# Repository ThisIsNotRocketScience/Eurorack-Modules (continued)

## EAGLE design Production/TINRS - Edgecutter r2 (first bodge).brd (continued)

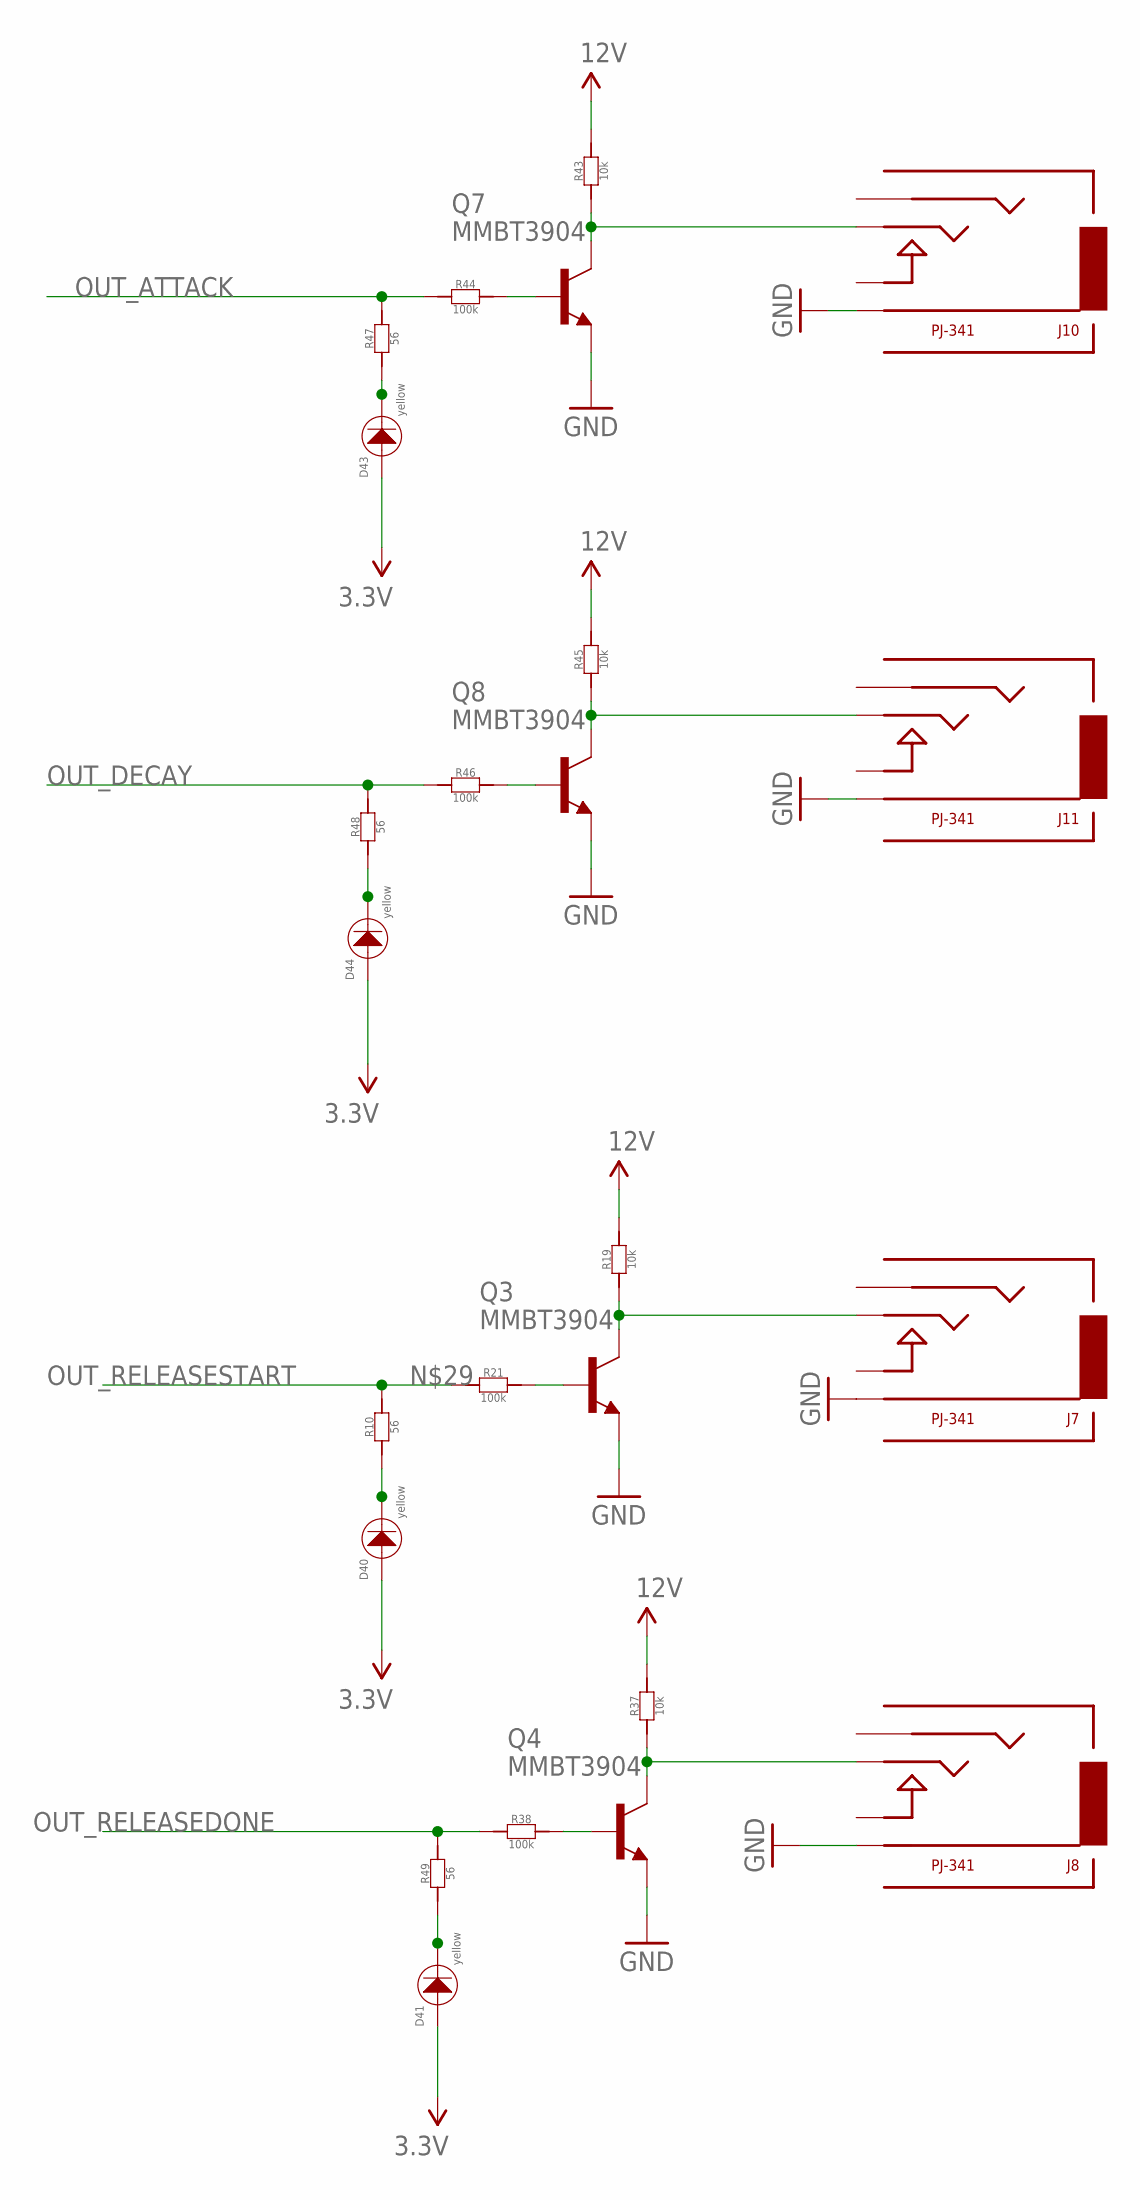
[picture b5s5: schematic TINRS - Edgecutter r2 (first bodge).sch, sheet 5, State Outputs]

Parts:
D40, D41, D43, D44: yellow; 3MMLED
J7, J8, J10, J11: PJ-341; 3.5MM-JACK-SWITCH-13MM-OUTPUT
Q3, Q4, Q7, Q8: MMBT3904; SOT23-BEC; MPN PMBT3904,215
R10, R47, R48, R49: 56; R0603
R19, R37, R43, R45: 10k; R0603
R21, R38, R44, R46: 100k; R0603

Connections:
3.3V: D40.+, D41.+, D43.+, D44.+; also elsewhere on the board
12V: R19.2, R37.2, R43.2, R45.2; also elsewhere on the board
D21: D43.-, R47.1
GND: J7.RING@3 (RING), J8.RING@3 (RING), J10.RING@3 (RING), J11.RING@3 (RING), Q3.E, Q4.E, Q7.E, Q8.E; also elsewhere on the board
unnamed: D40.-, R10.1
unnamed: Q3.B, R21.2
unnamed: J7.TIP@3 (TIP), Q3.C, R19.1
unnamed: D41.-, R49.1
unnamed: D44.-, R48.1
unnamed: Q4.B, R38.2
unnamed: J8.TIP@3 (TIP), Q4.C, R37.1
unnamed: Q7.B, R44.2
unnamed: J10.TIP@3 (TIP), Q7.C, R43.1
unnamed: Q8.B, R46.2
unnamed: J11.TIP@3 (TIP), Q8.C, R45.1
OUT_ATTACK: R44.1, R47.2; also elsewhere on the board
OUT_DECAY: R46.1, R48.2; also elsewhere on the board
OUT_RELEASEDONE: R38.1, R49.2; also elsewhere on the board
OUT_RELEASESTART: R10.2, R21.1; also elsewhere on the board

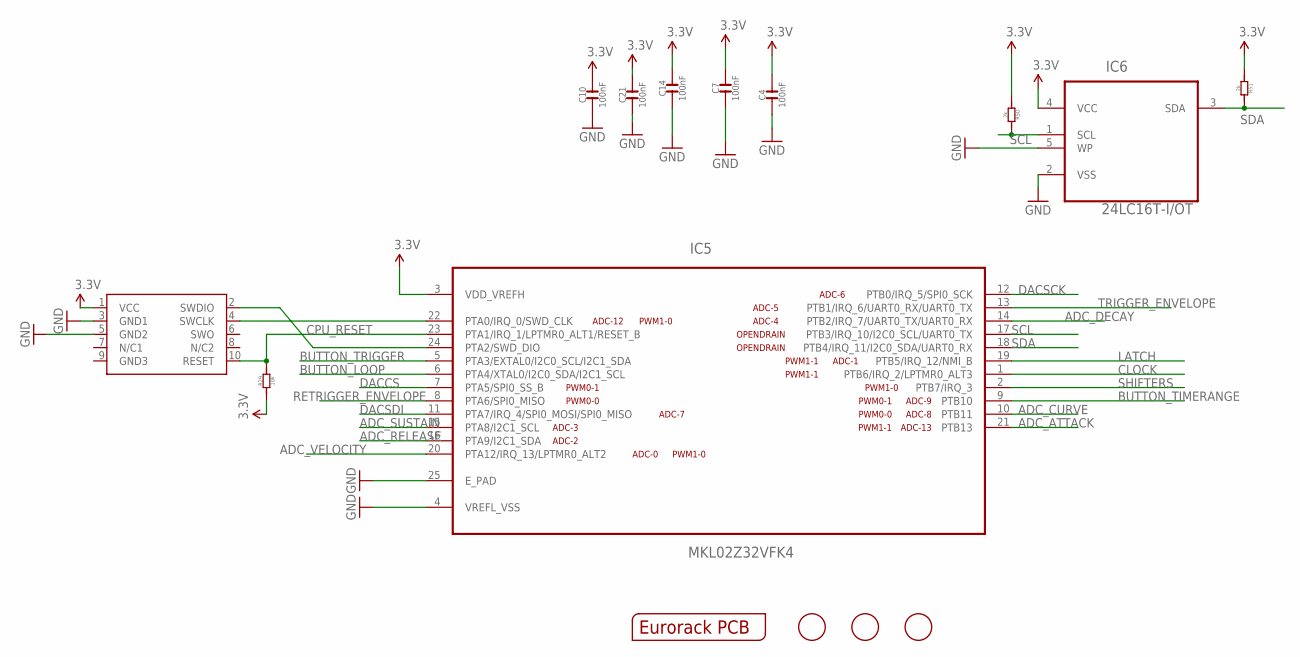
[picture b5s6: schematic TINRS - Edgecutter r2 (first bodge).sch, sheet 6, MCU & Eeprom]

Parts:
C4, C7, C10, C14, C21: 100nF; C0603; MPN MC0603F104Z160CT
FID1, FID2, FID3: FIDUCIAL; FIDUCIAL_1MM
IC5: MKL02Z32VFK4; QFN50P400X400X100-25N
IC6: 24LC16T-I/OT; SOT95P290X145-5N; MPN 24LC16T-I/OT
OUTLINE: EURORACK_PCB12HP; EURORACK12HPPCB
R29: 10k; R0603
R50, R51: 2k; R0603
SWD1: CORTEX_SWD; M50-3600542

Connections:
3.3V: C4.2, C7.2, C10.2, C14.2, C21.2, IC5.3 (VDD_VREFH), IC6.4 (VCC), R29.1, R50.1, R51.1, SWD1.1 (VCC); also elsewhere on the board
ADC_ATTACK: IC5.21 (PTB13); also elsewhere on the board
ADC_CURVE: IC5.10 (PTB11); also elsewhere on the board
ADC_DECAY: IC5.14 (PTB2/IRQ_7/UART0_TX/UART0_RX); also elsewhere on the board
ADC_RELEASE: IC5.16 (PTA9/I2C1_SDA); also elsewhere on the board
ADC_SUSTAIN: IC5.15 (PTA8/I2C1_SCL); also elsewhere on the board
ADC_VELOCITY: IC5.20 (PTA12/IRQ_13/LPTMR0_ALT2); also elsewhere on the board
BUTTON_LOOP: IC5.6 (PTA4/XTAL0/I2C0_SDA/I2C1_SCL); also elsewhere on the board
BUTTON_TIMERANGE: IC5.9 (PTB10); also elsewhere on the board
BUTTON_TRIGGER: IC5.5 (PTA3/EXTAL0/I2C0_SCL/I2C1_SDA); also elsewhere on the board
CLOCK: IC5.1 (PTB6/IRQ_2/LPTMR0_ALT3); also elsewhere on the board
CPU_RESET: IC5.23 (PTA1/IRQ_1/LPTMR0_ALT1/RESET_B), R29.2, SWD1.10 (RESET)
DACCS: IC5.7 (PTA5/SPI0_SS_B); also elsewhere on the board
DACSCK: IC5.12 (PTB0/IRQ_5/SPI0_SCK); also elsewhere on the board
DACSDI: IC5.11 (PTA7/IRQ_4/SPI0_MOSI/SPI0_MISO); also elsewhere on the board
GND: C4.1, C7.1, C10.1, C14.1, C21.1, IC5.4 (VREFL_VSS), IC5.25 (E_PAD), IC6.2 (VSS), IC6.5 (WP), SWD1.3 (GND1), SWD1.5 (GND2); also elsewhere on the board
LATCH: IC5.19 (PTB5/IRQ_12/NMI_B); also elsewhere on the board
RETRIGGER_ENVELOPE: IC5.8 (PTA6/SPI0_MISO); also elsewhere on the board
SCL: IC5.17 (PTB3/IRQ_10/I2C0_SCL/UART0_TX), IC6.1 (SCL), R50.2
SDA: IC5.18 (PTB4/IRQ_11/I2C0_SDA/UART0_RX), IC6.3 (SDA), R51.2
SHIFTERS: IC5.2 (PTB7/IRQ_3); also elsewhere on the board
SWD_CLK: IC5.22 (PTA0/IRQ_0/SWD_CLK), SWD1.4 (SWCLK)
SWD_DIO: IC5.24 (PTA2/SWD_DIO), SWD1.2 (SWDIO)
TRIGGER_ENVELOPE: IC5.13 (PTB1/IRQ_6/UART0_RX/UART0_TX); also elsewhere on the board

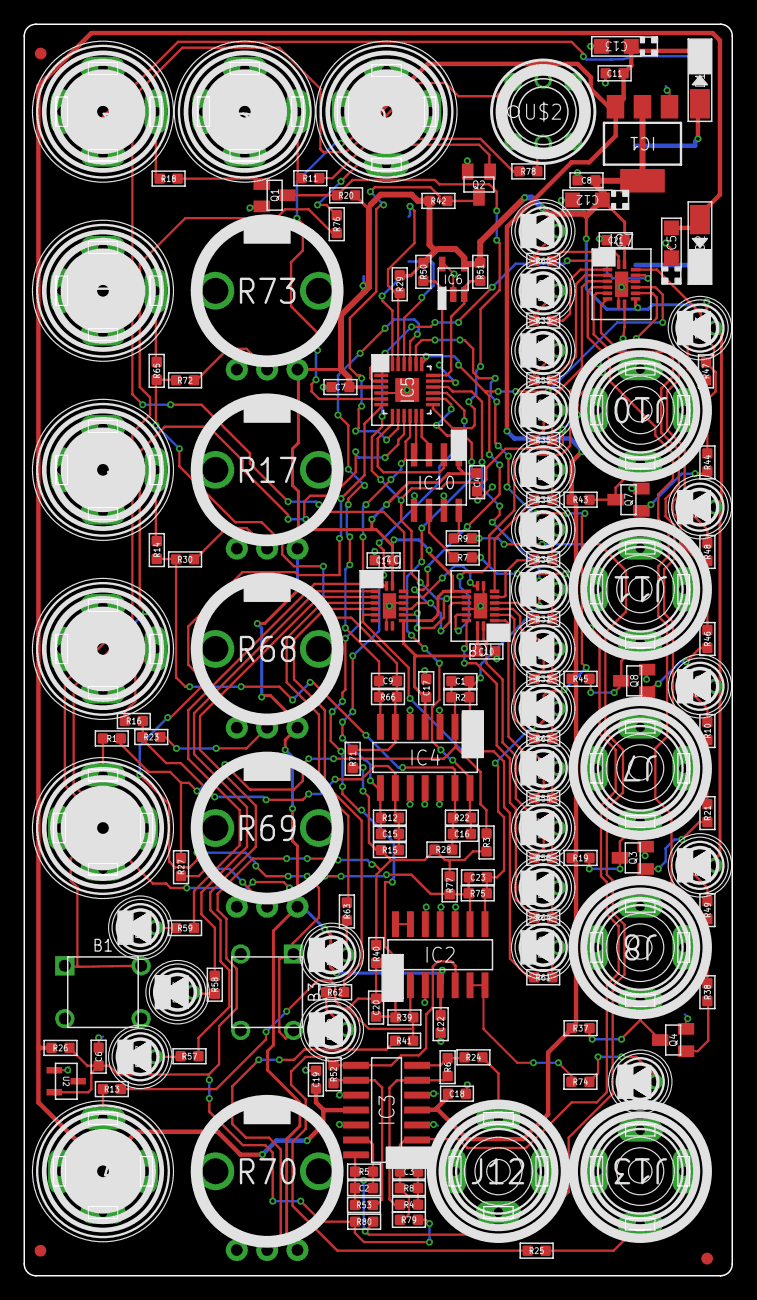
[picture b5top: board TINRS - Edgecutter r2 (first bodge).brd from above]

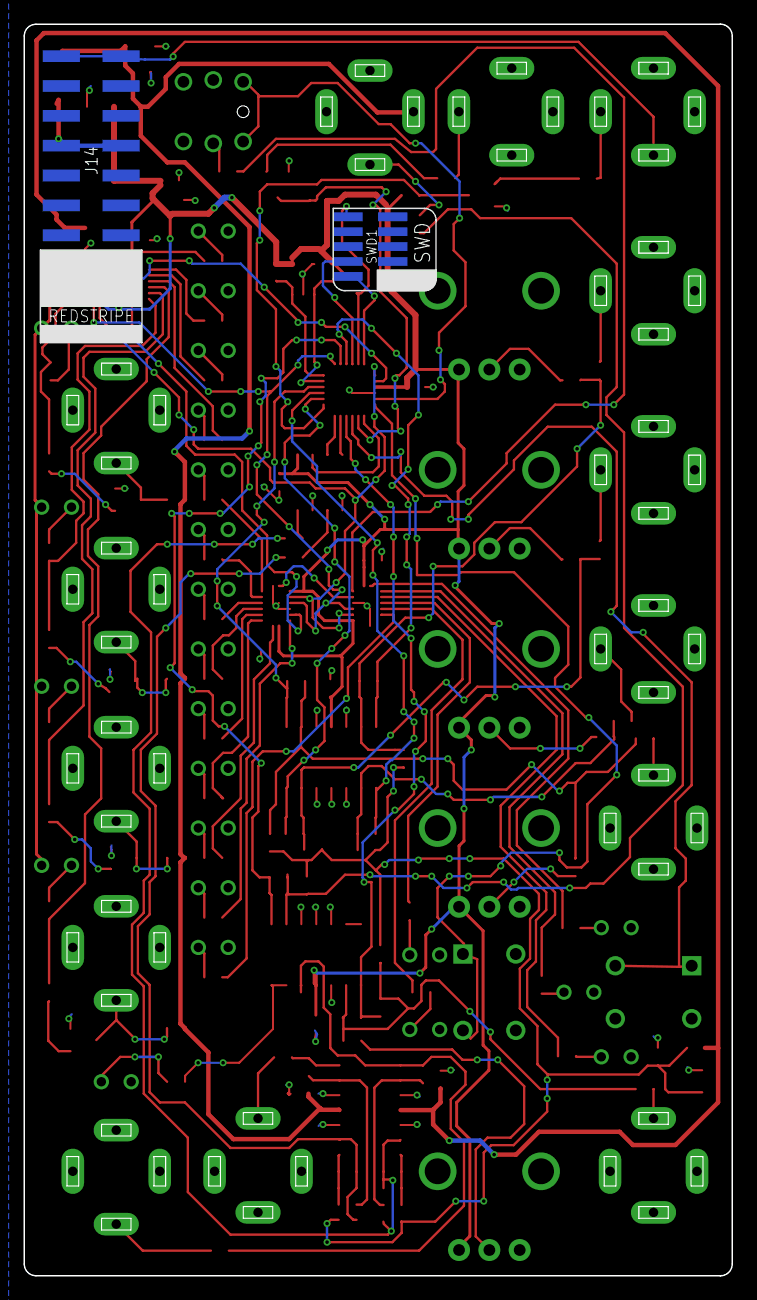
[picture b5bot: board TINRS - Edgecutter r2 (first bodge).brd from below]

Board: 2 copper layers, 60.2 x 106.5 mm, 168 parts (2 on the bottom side), 122 nets.
